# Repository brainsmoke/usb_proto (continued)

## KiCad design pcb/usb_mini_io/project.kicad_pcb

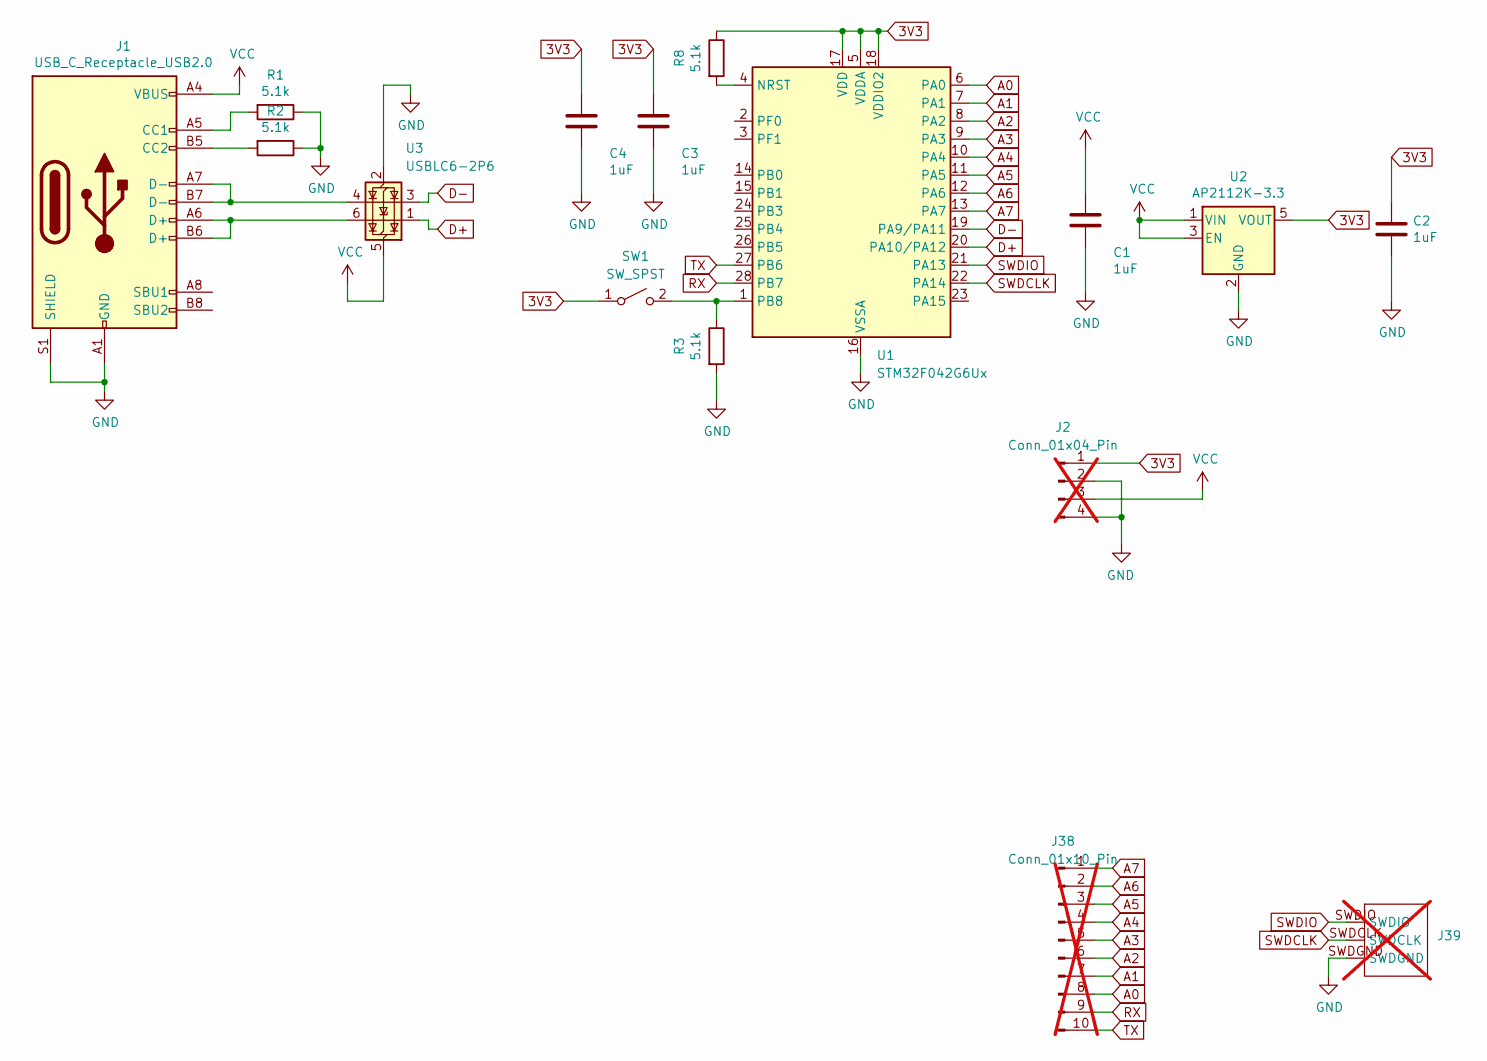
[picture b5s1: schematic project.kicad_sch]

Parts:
C1, C2, C3, C4: 1uF; C_0402_1005Metric; LCSC C52923
J1: USB_C_Receptacle_USB2.0; USB_C_Receptacle_HRO_TYPE-C-31-M-12; LCSC C165948
J2: Conn_01x04_Pin; PowerHeader; not fitted
J38: Conn_01x10_Pin; STM32IOHeader; not fitted
J39: SWDHeader_covered; not fitted
R1, R2, R3, R8: 5.1k; R_0402_1005Metric; LCSC C25905
SW1: SW_SPST; SW_Push_1P1T_NO_CK_KMR2; LCSC C318893
U1: STM32F042G6Ux; QFN-28_4x4mm_P0.5mm; LCSC C961597
U2: AP2112K-3.3; SOT-23-5; LCSC C51118
U3: USBLC6-2P6; SOT-666; LCSC C15999

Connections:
3V3: C2.1, C3.1, C4.1, J2.1, R8.1, SW1.1 (A), U1.5 (VDDA), U1.17 (VDD), U1.18 (VDDIO2), U2.5 (VOUT)
A0: J38.8, U1.6 (PA0)
A1: J38.7, U1.7 (PA1)
A2: J38.6, U1.8 (PA2)
A3: J38.5, U1.9 (PA3)
A4: J38.4, U1.10 (PA4)
A5: J38.3, U1.11 (PA5)
A6: J38.2, U1.12 (PA6)
A7: J38.1, U1.13 (PA7)
D+: U1.20 (PA10/PA12), U3.1 (I/O1)
D-: U1.19 (PA9/PA11), U3.3 (I/O2)
GND: C1.2, C2.2, C3.2, C4.2, J1.A1 (GND), J1.A12 (GND), J1.B1 (GND), J1.B12 (GND), J1.S1 (SHIELD), J2.2, J2.4, J39.SWDGND, R1.1, R2.1, R3.2, U1.16 (VSSA), U2.2 (GND), U3.2 (GND)
unnamed: J1.A5 (CC1), R1.2
unnamed: J1.B5 (CC2), R2.2
unnamed: J1.A6 (D+), J1.B6 (D+), U3.6 (I/O1)
unnamed: J1.A7 (D-), J1.B7 (D-), U3.4 (I/O2)
unnamed: R3.1, SW1.2 (B), U1.1 (PB8)
unnamed: R8.2, U1.4 (NRST)
RX: J38.9, U1.28 (PB7)
SWDCLK: J39.SWDCLK, U1.22 (PA14)
SWDIO: J39.SWDIO, U1.21 (PA13)
TX: J38.10, U1.27 (PB6)
VCC: C1.1, J1.A4 (VBUS), J1.A9 (VBUS), J1.B4 (VBUS), J1.B9 (VBUS), J2.3, U2.1 (VIN), U2.3 (EN), U3.5 (VBUS)

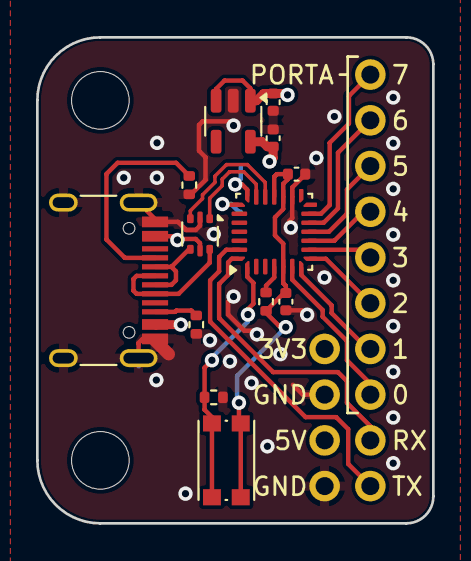
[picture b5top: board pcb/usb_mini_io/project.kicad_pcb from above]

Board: 2 copper layers, 22.0 x 27.0 mm, 16 parts (1 on the bottom side), 23 nets.

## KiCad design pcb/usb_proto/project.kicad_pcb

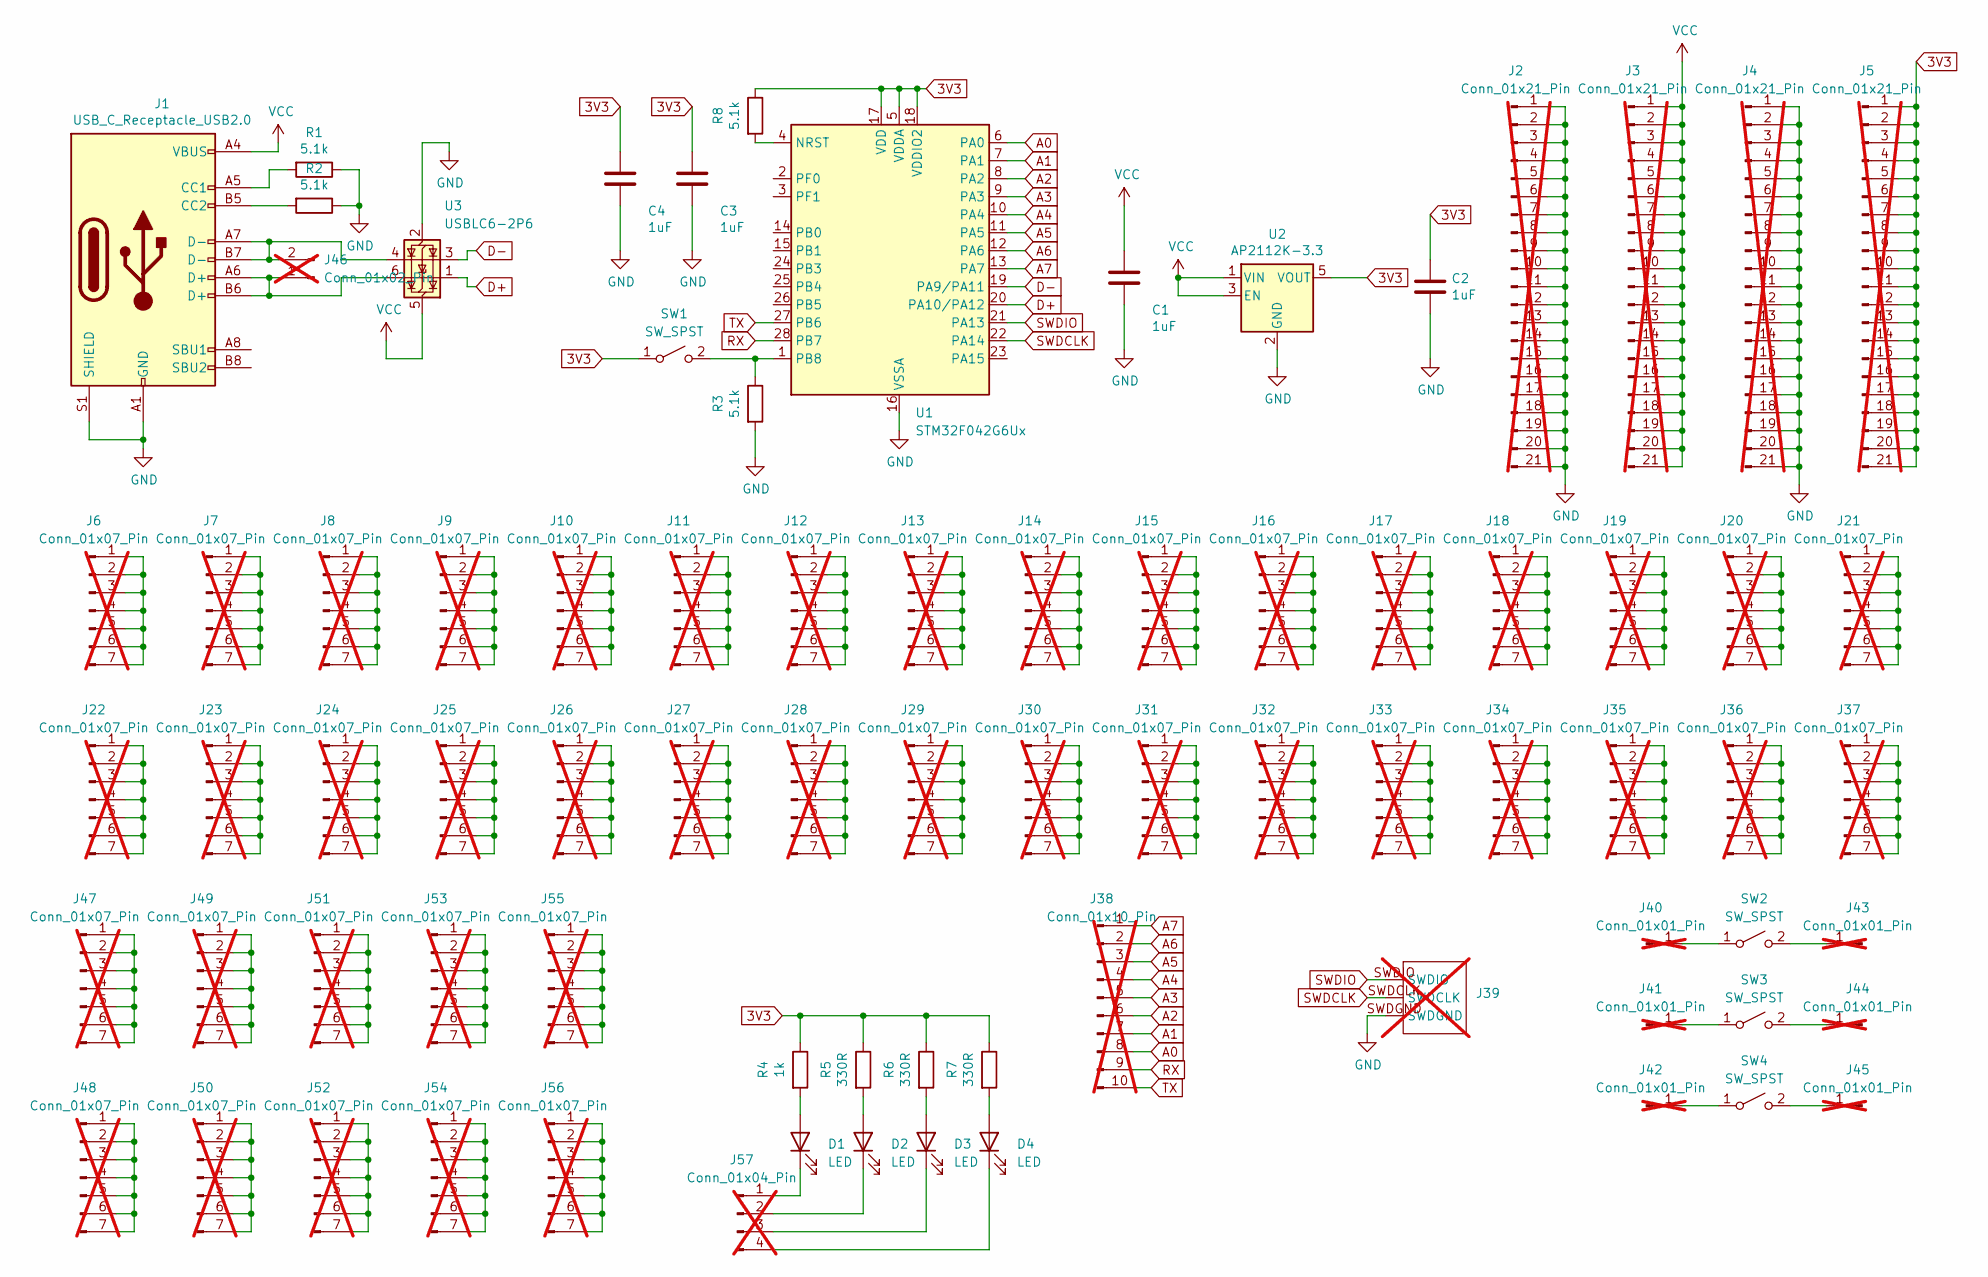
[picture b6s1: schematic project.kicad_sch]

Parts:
C1, C2, C3, C4: 1uF; C_0402_1005Metric; LCSC C52923
D1: LED; LED_0603_1608Metric; LCSC C2290
D2: LED; LED_0603_1608Metric; LCSC C12065
D3: LED; LED_0603_1608Metric; LCSC C72038
D4: LED; LED_0603_1608Metric; LCSC C2286
J1: USB_C_Receptacle_USB2.0; USB_C_Receptacle_HRO_TYPE-C-31-M-12; LCSC C165948
J2, J3, J4, J5: Conn_01x21_Pin; PinHeader_1x21_P2.54mm_Vertical; not fitted
J6, J7, J8, J9, J10, J11, J12, J13, J14, J15, J16, J17, J18, J19, J20, J21, J22, J23, J24, J25, J26, J27, J28, J29, J30, J31, J32, J33, J34, J35, J36, J37, J47, J48, J49, J50, J51, J52, J53, J54, J55, J56: Conn_01x07_Pin; PinHeader_1x07_P2.54mm_Vertical; not fitted
J38: Conn_01x10_Pin; STM32IOHeader; not fitted
J39: SWDHeader_through_hole; not fitted
J40, J41, J42, J43, J44, J45: Conn_01x01_Pin; PinSocket_1x01; not fitted
J46: Conn_01x02_Pin; PinHeader_1x02; not fitted
J57: Conn_01x04_Pin; PinHeader_1x04; not fitted
R1, R2, R3, R8: 5.1k; R_0402_1005Metric; LCSC C25905
R4: 1k; R_0402_1005Metric; LCSC C11702
R5, R6, R7: 330R; R_0402_1005Metric; LCSC C25104
SW1, SW2, SW3, SW4: SW_SPST; SW_Push_1P1T_NO_CK_KMR2; LCSC C318893
U1: STM32F042G6Ux; QFN-28_4x4mm_P0.5mm; LCSC C961597
U2: AP2112K-3.3; SOT-23-5; LCSC C51118
U3: USBLC6-2P6; SOT-666; LCSC C15999

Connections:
3V3: C2.1, C3.1, C4.1, J5.1, J5.2, J5.3, J5.4, J5.5, J5.6, J5.7, J5.8, J5.9, J5.10, J5.11, J5.12, J5.13, J5.14, J5.15, J5.16, J5.17, J5.18, J5.19, J5.20, J5.21, R4.1, R5.1, R6.1, R7.1, R8.1, SW1.1 (A), U1.5 (VDDA), U1.17 (VDD), U1.18 (VDDIO2), U2.5 (VOUT)
A0: J38.8, U1.6 (PA0)
A1: J38.7, U1.7 (PA1)
A2: J38.6, U1.8 (PA2)
A3: J38.5, U1.9 (PA3)
A4: J38.4, U1.10 (PA4)
A5: J38.3, U1.11 (PA5)
A6: J38.2, U1.12 (PA6)
A7: J38.1, U1.13 (PA7)
D+: U1.20 (PA10/PA12), U3.1 (I/O1)
D-: U1.19 (PA9/PA11), U3.3 (I/O2)
GND: C1.2, C2.2, C3.2, C4.2, J1.A1 (GND), J1.A12 (GND), J1.B1 (GND), J1.B12 (GND), J1.S1 (SHIELD), J2.1, J2.2, J2.3, J2.4, J2.5, J2.6, J2.7, J2.8, J2.9, J2.10, J2.11, J2.12, J2.13, J2.14, J2.15, J2.16, J2.17, J2.18, J2.19, J2.20, J2.21, J4.1, J4.2, J4.3, J4.4, J4.5, J4.6, J4.7, J4.8, J4.9, J4.10, J4.11, J4.12, J4.13, J4.14, J4.15, J4.16, J4.17, J4.18, J4.19, J4.20, J4.21, J39.SWDGND, R1.1, R2.1, R3.2, U1.16 (VSSA), U2.2 (GND), U3.2 (GND)
unnamed: D1.2 (A), R4.2
unnamed: D1.1 (K), J57.1
unnamed: D2.2 (A), R5.2
unnamed: D2.1 (K), J57.2
unnamed: D3.2 (A), R6.2
unnamed: D3.1 (K), J57.3
unnamed: D4.2 (A), R7.2
unnamed: D4.1 (K), J57.4
unnamed: J1.A5 (CC1), R1.2
unnamed: J1.B5 (CC2), R2.2
unnamed: J6.1, J6.2, J6.3, J6.4, J6.5, J6.6, J6.7
unnamed: J7.1, J7.2, J7.3, J7.4, J7.5, J7.6, J7.7
unnamed: J8.1, J8.2, J8.3, J8.4, J8.5, J8.6, J8.7
unnamed: J9.1, J9.2, J9.3, J9.4, J9.5, J9.6, J9.7
unnamed: J10.1, J10.2, J10.3, J10.4, J10.5, J10.6, J10.7
unnamed: J11.1, J11.2, J11.3, J11.4, J11.5, J11.6, J11.7
unnamed: J12.1, J12.2, J12.3, J12.4, J12.5, J12.6, J12.7
unnamed: J13.1, J13.2, J13.3, J13.4, J13.5, J13.6, J13.7
unnamed: J14.1, J14.2, J14.3, J14.4, J14.5, J14.6, J14.7
unnamed: J15.1, J15.2, J15.3, J15.4, J15.5, J15.6, J15.7
unnamed: J16.1, J16.2, J16.3, J16.4, J16.5, J16.6, J16.7
unnamed: J17.1, J17.2, J17.3, J17.4, J17.5, J17.6, J17.7
unnamed: J18.1, J18.2, J18.3, J18.4, J18.5, J18.6, J18.7
unnamed: J19.1, J19.2, J19.3, J19.4, J19.5, J19.6, J19.7
unnamed: J20.1, J20.2, J20.3, J20.4, J20.5, J20.6, J20.7
unnamed: J21.1, J21.2, J21.3, J21.4, J21.5, J21.6, J21.7
unnamed: J22.1, J22.2, J22.3, J22.4, J22.5, J22.6, J22.7
unnamed: J23.1, J23.2, J23.3, J23.4, J23.5, J23.6, J23.7
unnamed: J24.1, J24.2, J24.3, J24.4, J24.5, J24.6, J24.7
unnamed: J25.1, J25.2, J25.3, J25.4, J25.5, J25.6, J25.7
unnamed: J26.1, J26.2, J26.3, J26.4, J26.5, J26.6, J26.7
unnamed: J27.1, J27.2, J27.3, J27.4, J27.5, J27.6, J27.7
unnamed: J28.1, J28.2, J28.3, J28.4, J28.5, J28.6, J28.7
unnamed: J29.1, J29.2, J29.3, J29.4, J29.5, J29.6, J29.7
unnamed: J30.1, J30.2, J30.3, J30.4, J30.5, J30.6, J30.7
unnamed: J31.1, J31.2, J31.3, J31.4, J31.5, J31.6, J31.7
unnamed: J32.1, J32.2, J32.3, J32.4, J32.5, J32.6, J32.7
unnamed: J33.1, J33.2, J33.3, J33.4, J33.5, J33.6, J33.7
unnamed: J34.1, J34.2, J34.3, J34.4, J34.5, J34.6, J34.7
unnamed: J35.1, J35.2, J35.3, J35.4, J35.5, J35.6, J35.7
unnamed: J36.1, J36.2, J36.3, J36.4, J36.5, J36.6, J36.7
unnamed: J37.1, J37.2, J37.3, J37.4, J37.5, J37.6, J37.7
unnamed: J40.1, SW2.1 (A)
unnamed: J41.1, SW3.1 (A)
unnamed: J42.1, SW4.1 (A)
unnamed: J43.1, SW2.2 (B)
unnamed: J44.1, SW3.2 (B)
unnamed: J45.1, SW4.2 (B)
unnamed: J1.A6 (D+), J1.B6 (D+), J46.1, U3.6 (I/O1)
unnamed: J1.A7 (D-), J1.B7 (D-), J46.2, U3.4 (I/O2)
unnamed: J47.1, J47.2, J47.3, J47.4, J47.5, J47.6, J47.7
unnamed: J48.1, J48.2, J48.3, J48.4, J48.5, J48.6, J48.7
unnamed: J49.1, J49.2, J49.3, J49.4, J49.5, J49.6, J49.7
unnamed: J50.1, J50.2, J50.3, J50.4, J50.5, J50.6, J50.7
unnamed: J51.1, J51.2, J51.3, J51.4, J51.5, J51.6, J51.7
unnamed: J52.1, J52.2, J52.3, J52.4, J52.5, J52.6, J52.7
unnamed: J53.1, J53.2, J53.3, J53.4, J53.5, J53.6, J53.7
unnamed: J54.1, J54.2, J54.3, J54.4, J54.5, J54.6, J54.7
unnamed: J55.1, J55.2, J55.3, J55.4, J55.5, J55.6, J55.7
unnamed: J56.1, J56.2, J56.3, J56.4, J56.5, J56.6, J56.7
unnamed: R3.1, SW1.2 (B), U1.1 (PB8)
unnamed: R8.2, U1.4 (NRST)
RX: J38.9, U1.28 (PB7)
SWDCLK: J39.SWDCLK, U1.22 (PA14)
SWDIO: J39.SWDIO, U1.21 (PA13)
TX: J38.10, U1.27 (PB6)
VCC: C1.1, J1.A4 (VBUS), J1.A9 (VBUS), J1.B4 (VBUS), J1.B9 (VBUS), J3.1, J3.2, J3.3, J3.4, J3.5, J3.6, J3.7, J3.8, J3.9, J3.10, J3.11, J3.12, J3.13, J3.14, J3.15, J3.16, J3.17, J3.18, J3.19, J3.20, J3.21, U2.1 (VIN), U2.3 (EN), U3.5 (VBUS)

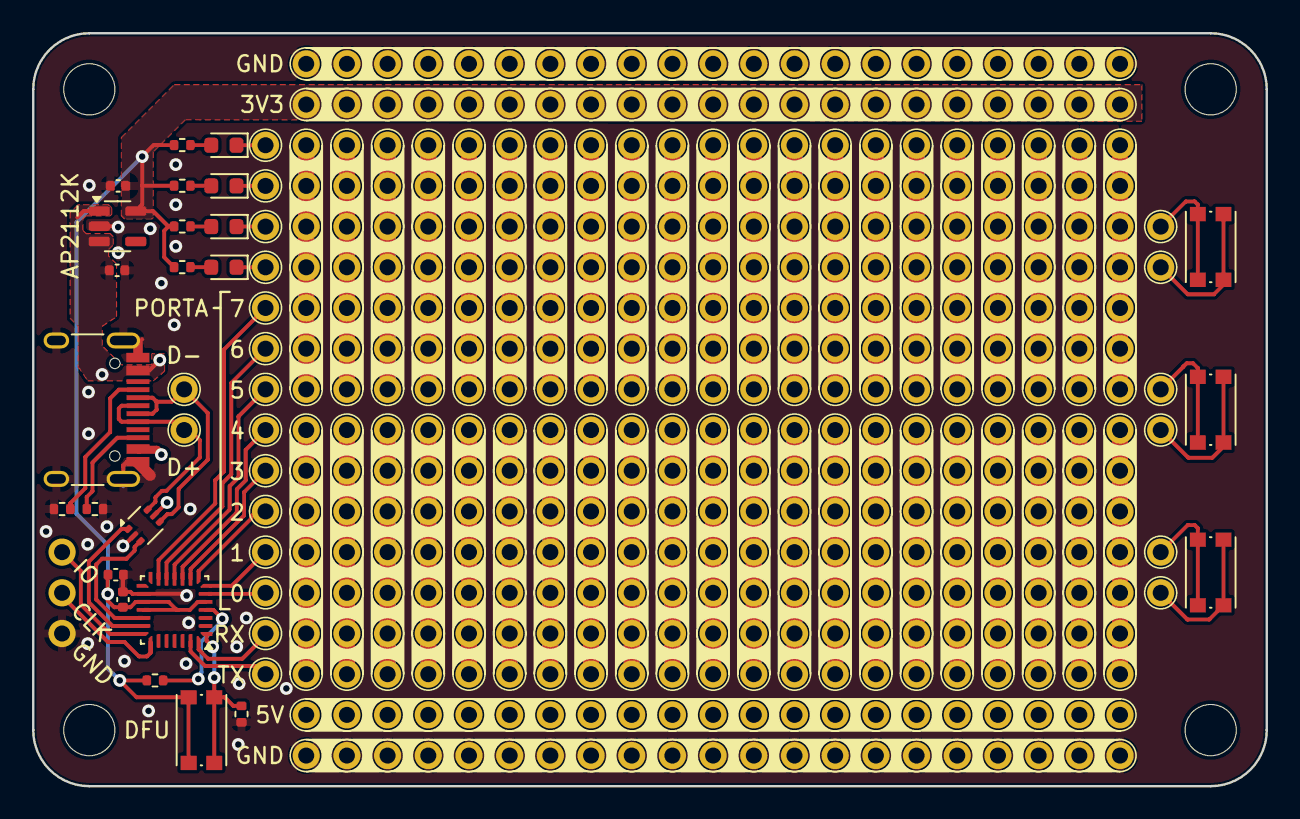
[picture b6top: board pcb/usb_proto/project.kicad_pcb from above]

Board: 2 copper layers, 77.0 x 47.0 mm, 80 parts (0 on the bottom side), 79 nets.

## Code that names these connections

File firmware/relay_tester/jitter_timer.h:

#ifndef JITTER_TIMER_H
#define JITTER_TIMER_H


#define ROUTING5 (0x300)
#define ROUTING4 (0x100)
#define VALUE   (0x000)

#define HISTOGRAM_MAX (0x80)

#define LED_HIDDEN  (0)
#define LED0  (4)
#define LED1  (8)
#define LED2 (12)
#define LED3 (16)

#define ROUTE5_PACKET (3)
#define PACKET1  (7)
#define PACKET2  (11)
#define PACKET3  (15)

#define BITBANG_NATIVE_CYCLES (70)

//#define MEASURE_LEN            (1024)
#define MEASURE_LEN            (64)
#define MEASURE_PERIODS        (MEASURE_LEN*8-1)
#define MEASURE_NATIVE_CYCLES  (BITBANG_NATIVE_CYCLES*MEASURE_PERIODS)
#define FRAME_LEN              (MEASURE_LEN+PACKET3+1)

#ifndef __ASSEMBLER__

#include <stdint.h>

extern uint32_t histogram[HISTOGRAM_MAX+1];
void bitbang(uint16_t *buf, uint32_t pin, uint32_t gpio, uint32_t timer);

void bitbang_clear(uint32_t gpio, uint32_t mask);

#endif

#endif // JITTER_TIMER_H

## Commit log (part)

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2024-06-17 usb protoboard
2024-06-17 add image
2024-07-03 add photo
2024-07-03 bigger image
2024-07-04 JLC order
2024-07-11 add (tweakable) case
2024-07-11 tweak usb c cut-out
2024-08-22 add CC-BY-4.0 LICENCE
2024-09-07 scad: provide .stl
    Provide a pregenerated STL from the default settings so I can directly
    drag and drop into my slicer.
2024-09-07 doc: photo that includes the case
    A new photo for the README that displays the case as well.
2024-09-07 organisation: subdirectories for pcb and cad
    Moves the pcb design files into a separate subdirectory which is
    opinionated. Renames the scad directory to the more common cad.
2024-09-07 doc: write some text
    Use markdown syntax (and provide alt-text) for the README. Also write a
    tiny blurb about what the repository actually contains.
2024-09-08 organisation: img subdir
2024-09-08 move pcb files to pcb dir
2024-09-08 move images
2024-09-08 rename directory with case files
2024-09-08 fix link
2024-09-08 typo
2024-09-11 fix merge gone weird
2024-09-11 add new case design
2024-09-11 add stl with case+top
2024-09-13 fix grid center
2024-09-21 add stm32 for usb-serial
2024-09-21 add production file Makefile
2024-09-21 fix posfile
2024-09-21 adjust case parameters
2024-09-21 add oshw logo
2024-09-22 move pcb to subdirectory
2024-09-22 rename project files
2024-09-22 add multi-project Makefile
2024-09-22 add usb serial capable protoboard
2024-09-22 add generated stls
2024-09-22 remove old Makefile
2024-09-22 add production files (untested)
2024-09-22 Makefile cleanup
2024-09-22 fix bomfile generation (untested)
2024-09-23 RUN DRC
2024-09-24 usbserial v0.2
2024-09-24 adjust the case's PCB thickness to what I ordered
2024-09-24 add LEDs to BOM, turn power LED into general purpose LED
2024-09-24 give original protoboard a separate directory
2024-09-24 use M3 bolts for the simple protoboard
2024-09-24 split parameters file to speed up builds
2024-09-25 fix separate case top/bottom .stl generation
2024-09-25 slightly thinner grid to make slicer happy
2024-09-29 add optional buttons to case
2024-09-29 split off rules.mk
2024-09-29 generalize stl generating rules
2024-09-29 orient top parts correctly for 3d printing
2024-09-30 make define rule work in the general case
2024-09-30 slight flexture improvement
2024-09-30 add OSHW logo / CC license text
2024-09-30 remove obsolete project files
2024-10-01 fix image link
2024-10-15 add initial usb serial code
2024-10-15 edit readme
2024-10-15 modify usb serial API
2024-10-15 change usb serial/product/manufacturer strings
2024-10-15 fix usb serial code
2024-10-19 add line state/coding notifications
2024-10-19 consistency
2024-10-19 tabs
2024-10-20 add blocking write
2024-10-20 split simple demo
2024-10-20 untested
2024-10-20 reorder functions, still untested
2024-10-26 looks like it works
    not sure if there's a thing in the descriptor to make
    noecho (raw) the default.
2024-10-26 remove commented-out debug code
2024-10-27 add set_line_options (baudrate etc.) untested
2024-10-27 add resistor to NRST pull-up
2024-10-27 add optional DFU button to case
2024-10-27 fix serial state request type
2024-10-28 serial code untested
2024-10-29 fix baudrate setting
2024-10-29 adjust image size
2024-10-29 add dfu
2024-10-30 add .gitignore
2024-10-31 double buffering, untested
2024-11-02 totally broken
2024-11-02 still broken, but less so
2024-11-02 re-add gpio code, not at fault, the rest is still broken
2024-11-02 fixed obvious bug, still very much untested
2024-11-03 still broken
2024-11-03 bug found
2024-11-03 catch stall request to prevent potential messing with toggle bits
2024-11-03 remove debug aid
2024-11-03 fix inconsequential bug
2024-11-07 add keypad code
2024-11-07 add hid keyboard (untested)
2024-11-07 fix typo/add decription
2024-11-07 indentatioon
2024-11-07 simple hid keyboard (untested
2024-11-07 fix filename
2024-11-07 add firmware description
2024-11-07 add missing image
2024-11-07 add untested description
2024-11-08 test & fix keypad code
2024-11-08 add comment
2024-11-24 make swd header through hole and accessible
2024-11-27 add descriptors for boot-compatible keyboard & mouse
2024-11-29 add ESD protection diodes
2024-11-29 add usb serial firmware dfu
2024-12-24 add missing dependency to Makefile
2024-12-24 make usbserial case the default
2024-12-24 add ledrelay tested scad file
2024-12-24 add led segment tester
2024-12-25 add build files to gitignore
2024-12-25 rename pcb from 'usbserial' to 'mcu'
2024-12-28 improve error 'reporting'
2024-12-28 different color LEDs
2025-01-02 fix bug in led segment tester / add passive test
2025-01-03 allow for testing multiple segments
2025-01-05 add light pipes code
2025-01-05 mae lightpipes / buttons default for case
2025-01-05 add blink example
2025-01-06 adjust LED brightness, fix red LED off state when connected to MCU
2025-01-06 use one less resistor type
2025-01-10 make adding features to the top easier
2025-01-10 tweak wall thicknesses
2025-01-11 add keswitch top covers
2025-01-11 add hexagonal case
2025-01-11 tweak hexagonal case
2025-01-15 fix glitches in preview
2025-01-17 rotate case model to match with kicad orientation
2025-01-18 add led strip connectors
2025-01-18 rename sculpt -> graft
2025-01-18 add stl
2025-02-15 add subodule checkout to build instructions
2025-03-02 change LED order
2025-05-27 add more cases
2025-06-14 make esp32 programmer signals work nicely with external button presses
2025-06-20 update dfu
2025-06-22 untested IKEA OBEGRÄNSAD driver example
2025-06-22 fix readme
2025-06-23 fix usb serial read before endpoint negotiation
2025-06-23 add button presses
2025-06-23 improve REAMDE
2025-06-24 README: add picture
2025-06-25 make millisecond counter part of the common lib
2025-06-29 rename keypad.[ch] to keymatrix.[ch]
2025-06-30 reduce number of defines needed to configure keyboard matrix
2025-06-30 add 32 bit millisecond time
2025-07-01 make key scanning slightly faster
2025-07-25 add usb serial firware for stmmini board
2025-09-04 add led segment tested v2
2025-09-14 add up-to-date dfu
2025-09-14 add debug scripts
2025-09-14 update Makefile
2025-09-14 move STLs to build dir
2026-02-18 strip KEY_NONE in usb hid descriptor
2026-02-23 make KEY_NONE default in array initializations (by making the constant 0)
2026-04-29 add board without the proto space
2026-04-29 use up-to-date posfile_to_boardhouse.py
2026-04-29 rename internal Makefile vars / fix make clean
2026-05-05 add case for tiny pcb
2026-05-07 move keyswitch to its own file
2026-05-07 adjust keyswitch hole tolerances
2026-05-07 ignore kicad_prl files
2026-05-07 update stl build files for keyswitches
2026-05-07 use pcb_shape() module to cut out space for the PCB.
2026-05-09 add mx keyswitch mockup/keep-out zone
2026-05-09 add keystem to mx key mockup
2026-05-10 only remove pcb holes from pcb
2026-05-10 change default keypad pitch to 20mm
2026-05-10 rename case_tiny_keyswitches_* -> keypad_proud*_tiny_mcu
2026-05-10 add keypad enclosure with no gap between the keys and the case
2026-05-11 add keypad stl generating script
2026-05-11 mk_keypad.sh: complain about openscad not in $PATH
2026-05-12 add links to buildfiles
2026-05-12 add more links to README
2026-05-12 minor readme edit
2026-05-13 put keys in config.h
2026-05-13 add popcalc machine
2026-05-13 add popcalc photo
2026-05-13 change USB descriptor for popcalc
2026-05-14 add retainer clip to cases for the breakout board
2026-05-14 tweak retainer clip
2026-05-14 add keypad stl as build files
2026-05-14 readme reshuffle
2026-05-14 increase distance between keyswitch and board
2026-05-14 add flappy bird controller / case
2026-05-14 remove extra redundant superfluosity in the README
2026-05-16 add game controller case
2026-05-16 add dfu_button to game controller
2026-05-17 parameterize game controller
2026-05-17 remove unused & misleading parameter
2026-05-17 copy up-to-date hid_keydef from keyboard repo
2026-05-17 add game controller hid device code
2026-05-17 deduplicate code
2026-05-17 [firmwae/game_controller] add image/circuit to README
2026-05-17 [firmware/gmae_controller] extra picture
2026-05-19 rename keypad files
2026-05-19 update mk_keypad script to use the renamed files
2026-05-20 [case] make the height of the border of the lid independent of its overall thickness
2026-05-20 don't unnecessarily poke holes in grafted objects for screw guides
2026-05-20 render cases by default to get rid of artifacts
2026-05-20 make grids slightly more generic
2026-05-20 [case] add chamfers
2026-05-20 fix grids
2026-05-21 change some defaults
2026-05-21 update STLs
2026-05-21 restore top border size
2026-05-21 decrease keypad height
2026-05-21 update STLs (restore top border)
2026-05-21 fix README formatting
2026-05-21 really fix readme formatting
2026-05-22 make graft API more consistent
2026-05-23 simplefy & improve chamfers
2026-05-23 don't count chamfer with top_border height
2026-05-31 make screw guides take chamfers into account
2026-06-01 add sanity assertions for chamfers
2026-06-01 fix assertions (ooops)
2026-06-05 rename PCBs
2026-06-05 fix images in readme
2026-06-05 fix REAMDE links
2026-06-05 use refactored case generator
2026-06-05 fix broken links in README
2026-06-06 render components from kicad pcbs in preview / Makefile tweaks
2026-06-06 remove unused parameter files
2026-06-06 move mk_keypad.sh
2026-06-07 add flexible key matrix pcb
2026-06-07 add missing pads to usb_proto pcb openscad model
2026-06-08 add usb 'null modem' board
2026-06-08 [usb_hid_keymatrix] put key configuration in config.h
2026-06-08 rotate matrix pcb to make the rows the select line
2026-06-08 fix keymatrix orientation in code & documentation
2026-06-08 add 5x5 keymatrix
2026-06-08 add 5x5 keymatrix to README
2026-06-08 perfect openscad bounding box generatiion
2026-06-09 fix row calc shift
2026-06-09 don't include mockup in the render
2026-06-13 move firmware section to top the README
2026-06-30 fix keypad code
